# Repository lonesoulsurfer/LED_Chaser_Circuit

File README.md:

LED Chaser

The circuit was put together to add some life to a little Junkbot I made from a vintage shaver and umbrella!

The circuit is your classic ' Knight Rider' style LED chaser.  The LED's move left to right and the speed is controlled via a light dependent resistor - the darker it is the slower the LED move.

YouTube - https://www.youtube.com/shorts/1Rffqpa6rq4

Instructable - TBA

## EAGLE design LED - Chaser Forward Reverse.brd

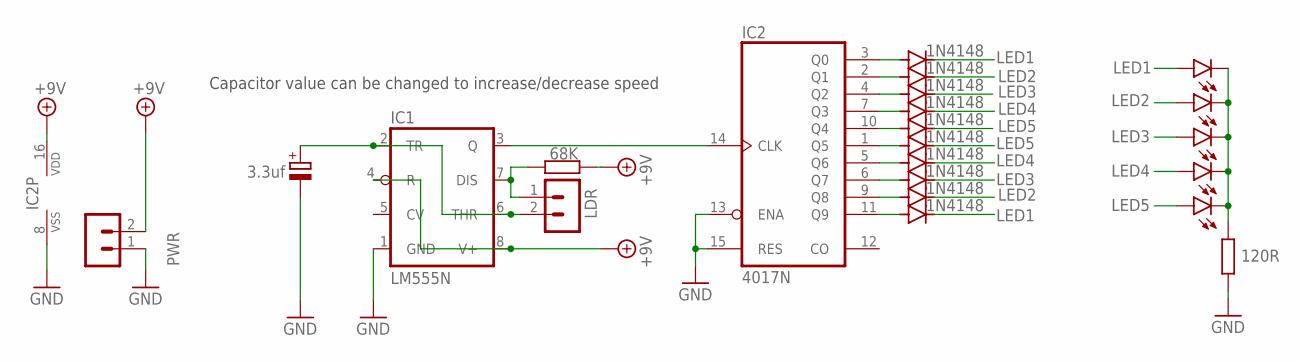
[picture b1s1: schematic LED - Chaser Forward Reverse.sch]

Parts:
C1: 3.3uf; E2,5-5
D1, D2, D3, D4, D5, D6, D7, D8, D9, D10: 1N4148; DO35-7
IC1: LM555N; DIL08
IC2: 4017N; DIL16
LDR: B2B-PH-K-S
LED1, LED2, LED3, LED4, LED5: LED3MM
PWR: B2B-PH-K-S
R1: 68K; 0207/10
R2: 120R; 0207/10

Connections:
+9V: IC1.4 (R), IC1.8 (V+), IC2.16 (VDD), PWR.2, R1.2
GND: C1.-, IC1.1 (GND), IC2.8 (VSS), IC2.13 (ENA), IC2.15 (RES), PWR.1, R2.1
LED1: D1.C, D10.C, LED1.A
LED2: D2.C, D9.C, LED2.A
LED3: D3.C, D8.C, LED3.A
LED4: D4.C, D7.C, LED4.A
LED5: D5.C, D6.C, LED5.A
unnamed: IC1.7 (DIS), LDR.1, R1.1
unnamed: C1.+, IC1.2 (TR), IC1.6 (THR), LDR.2
unnamed: IC1.3 (Q), IC2.14 (CLK)
unnamed: LED1.K (C), LED2.K (C), LED3.K (C), LED4.K (C), LED5.K (C), R2.2
unnamed: D1.A, IC2.3 (Q0)
unnamed: D2.A, IC2.2 (Q1)
unnamed: D3.A, IC2.4 (Q2)
unnamed: D4.A, IC2.7 (Q3)
unnamed: D5.A, IC2.10 (Q4)
unnamed: D6.A, IC2.1 (Q5)
unnamed: D7.A, IC2.5 (Q6)
unnamed: D8.A, IC2.6 (Q7)
unnamed: D9.A, IC2.9 (Q8)
unnamed: D10.A, IC2.11 (Q9)

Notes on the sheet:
Capacitor value can be changed to increase/decrease speed

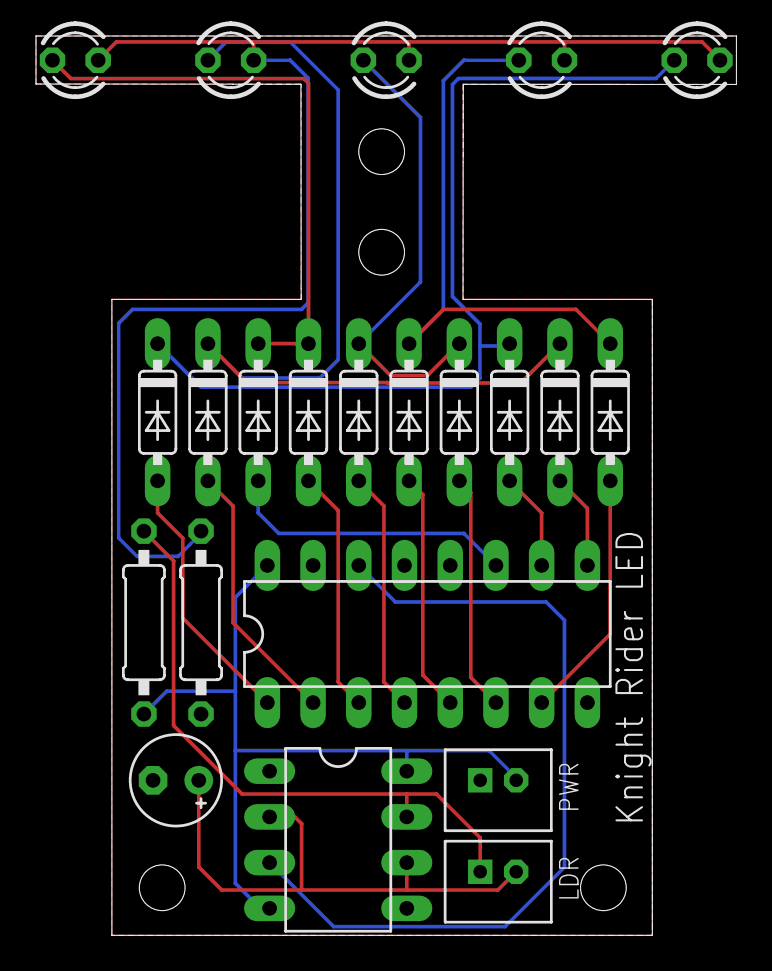
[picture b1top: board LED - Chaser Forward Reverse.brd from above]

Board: 2 copper layers, 38.9 x 50.0 mm, 22 parts (0 on the bottom side), 21 nets.
